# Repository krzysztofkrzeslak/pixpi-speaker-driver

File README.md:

# pixpi-sound-sensor
Repository which holds speaker driver sources(schematic and board)for PiXPi controller <br/>

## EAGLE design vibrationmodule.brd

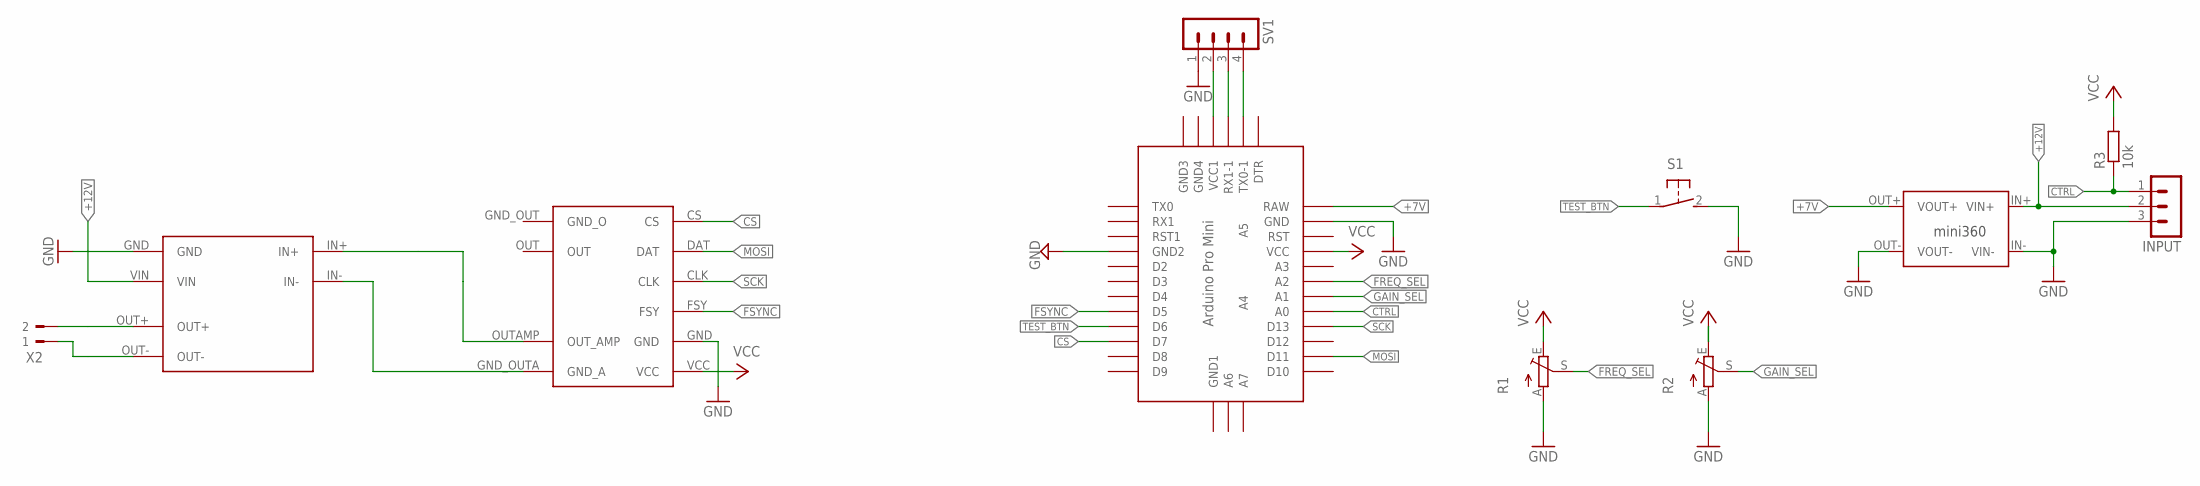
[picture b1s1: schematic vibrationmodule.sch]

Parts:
INPUT: MA03-1
R1, R2: TRIM_EU-CA9H; CA9H
R3: 10k; M0805
S1: 31-XX; B3F-31XX
SV1: MA04-1
U$1: AD9833AMP
U$2: MINI360
U$3: HW328
U$5: ABK-PRO-MINI
X2: 90-2

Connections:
+7V: U$2.OUT+ (VOUT+), U$5.RAW
+12V: INPUT.2, U$2.IN+ (VIN+), U$3.VIN
CS: U$1.CS, U$5.D7
CTRL: INPUT.1, R3.1, U$5.A0
FREQ_SEL: R1.S, U$5.A2
FSYNC: U$1.FSY, U$5.D5
GAIN_SEL: R2.S, U$5.A1
GND: R1.A, R2.A, S1.2 (S), SV1.1, U$1.GND, U$2.OUT- (VOUT-), U$5.GND
GND1: INPUT.3, U$2.IN- (VIN-), U$3.GND
GND2: U$5.GND1 (GND2)
MOSI: U$1.DAT, U$5.D11
unnamed: U$1.OUTAMP (OUT_AMP), U$3.IN+
unnamed: SV1.4, U$5.TX0-1
unnamed: U$3.OUT+, X2.2
unnamed: U$1.GND_OUTA (GND_A), U$3.IN-
unnamed: SV1.3, U$5.RX1-1
unnamed: SV1.2, U$5.VCC1
unnamed: U$3.OUT-, X2.1
SCK: U$1.CLK, U$5.D13
TEST_BTN: S1.1, U$5.D6
VCC: R1.E, R2.E, R3.2, U$1.VCC, U$5.VCC

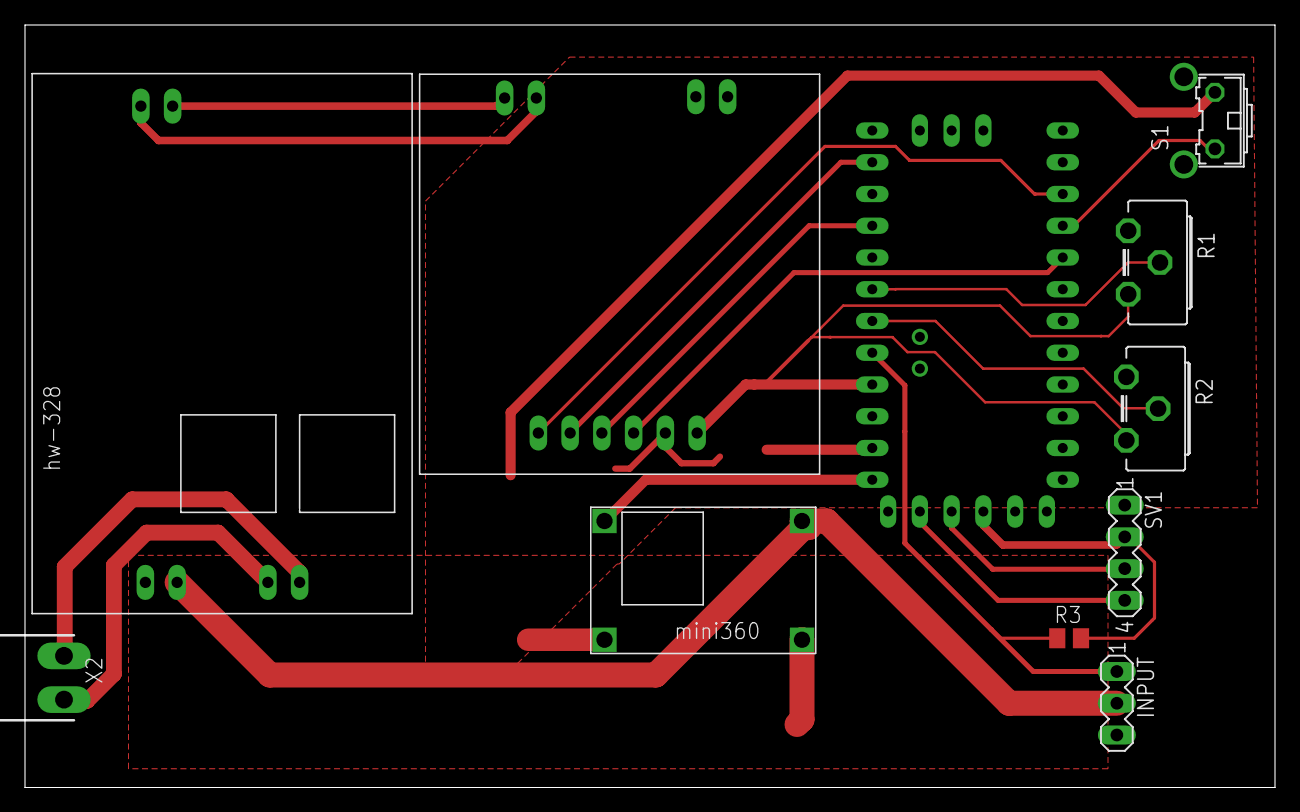
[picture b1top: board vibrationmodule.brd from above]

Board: 2 copper layers, 100.0 x 61.0 mm, 11 parts (0 on the bottom side), 20 nets.

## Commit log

2019-08-23 Added schematic, board and readme
